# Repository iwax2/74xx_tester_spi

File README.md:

# 74xx_tester_spi

電気系の実験で用いる74LSxxシリーズ、学校の実験で壊れているかどうかチェックするのが大変なので、簡単にテストできるテス
タを作りました。
Arduinoシールド型（ちょっとでかい）で、0.5秒ぐらいでICを1つテストできます。
これはSPIでI/Oエキスパンダ(MCP23S17-E/SP)を接続するバージョンです。I2Cの(MCP23017-E/SP)も作る予定。

## つかうもの
* Arduino uno(互換品でも可)
* MCP23S17-E/SP(<http://akizukidenshi.com/catalog/g/gI-10644/>)
* ArduinoのLiquidCrystalクラスが使えるLCD(SC162Cなど)
* 14pin以上のソケット(できればゼロプレッシャー) こんなの -> <http://www.aitendo.com/product/12374>
* タクトスイッチ2つ
* Arduinoシールド台（基板加工機を使って作る、PCB製造業者に依頼する、自分でエッチングする、Arduino用のユニバーサル基板シールドを加工する、[ユニバーサル](http://diary-kuzenikike.blogspot.jp/2010/03/arduino.html "Arduino用のユニバーサル基板をつくる")[基板Cで頑張る](http://memo.tank.jp/archives/1182 "頑丈な自作プロトシールド")　など）

## 対応IC
*  "IV1 (74LS04)", // 1-input NOT
*  "AN2 (74LS08)", // 2-input AND
*  "OR2 (74LS32)", // 2-input OR
*  "ND2 (74LS00)", // 2-input NAND
*  "NR2 (74LS02)", // 2-input NOR
*  "EO2 (74LS86)", // 2-input XOR
*  "DFF (74LS74)"  // D flip-flop

## つかいかた
1. Arduinoにシールドを指します
2. テストしたいICをゼロプレッシャーソケットにセットします
3. セットしたICの型番をselectボタンで選択します
4. testボタンを押して、OKが出れば正常、NGが出れば壊れています

## Arduinoへのスケッチの書き込み
`tester_74xx_spi.ino`をArduino IDE (1.6.11で確認)で書き込んでください

## demo

## Pictures

全体写真

Arduinoシールドとして利用できる

テストした結果がOKの場合（壊れていないIC）

テストした結果がNGの場合（壊れているIC）

基板加工機(MITS AutoLab)で作成

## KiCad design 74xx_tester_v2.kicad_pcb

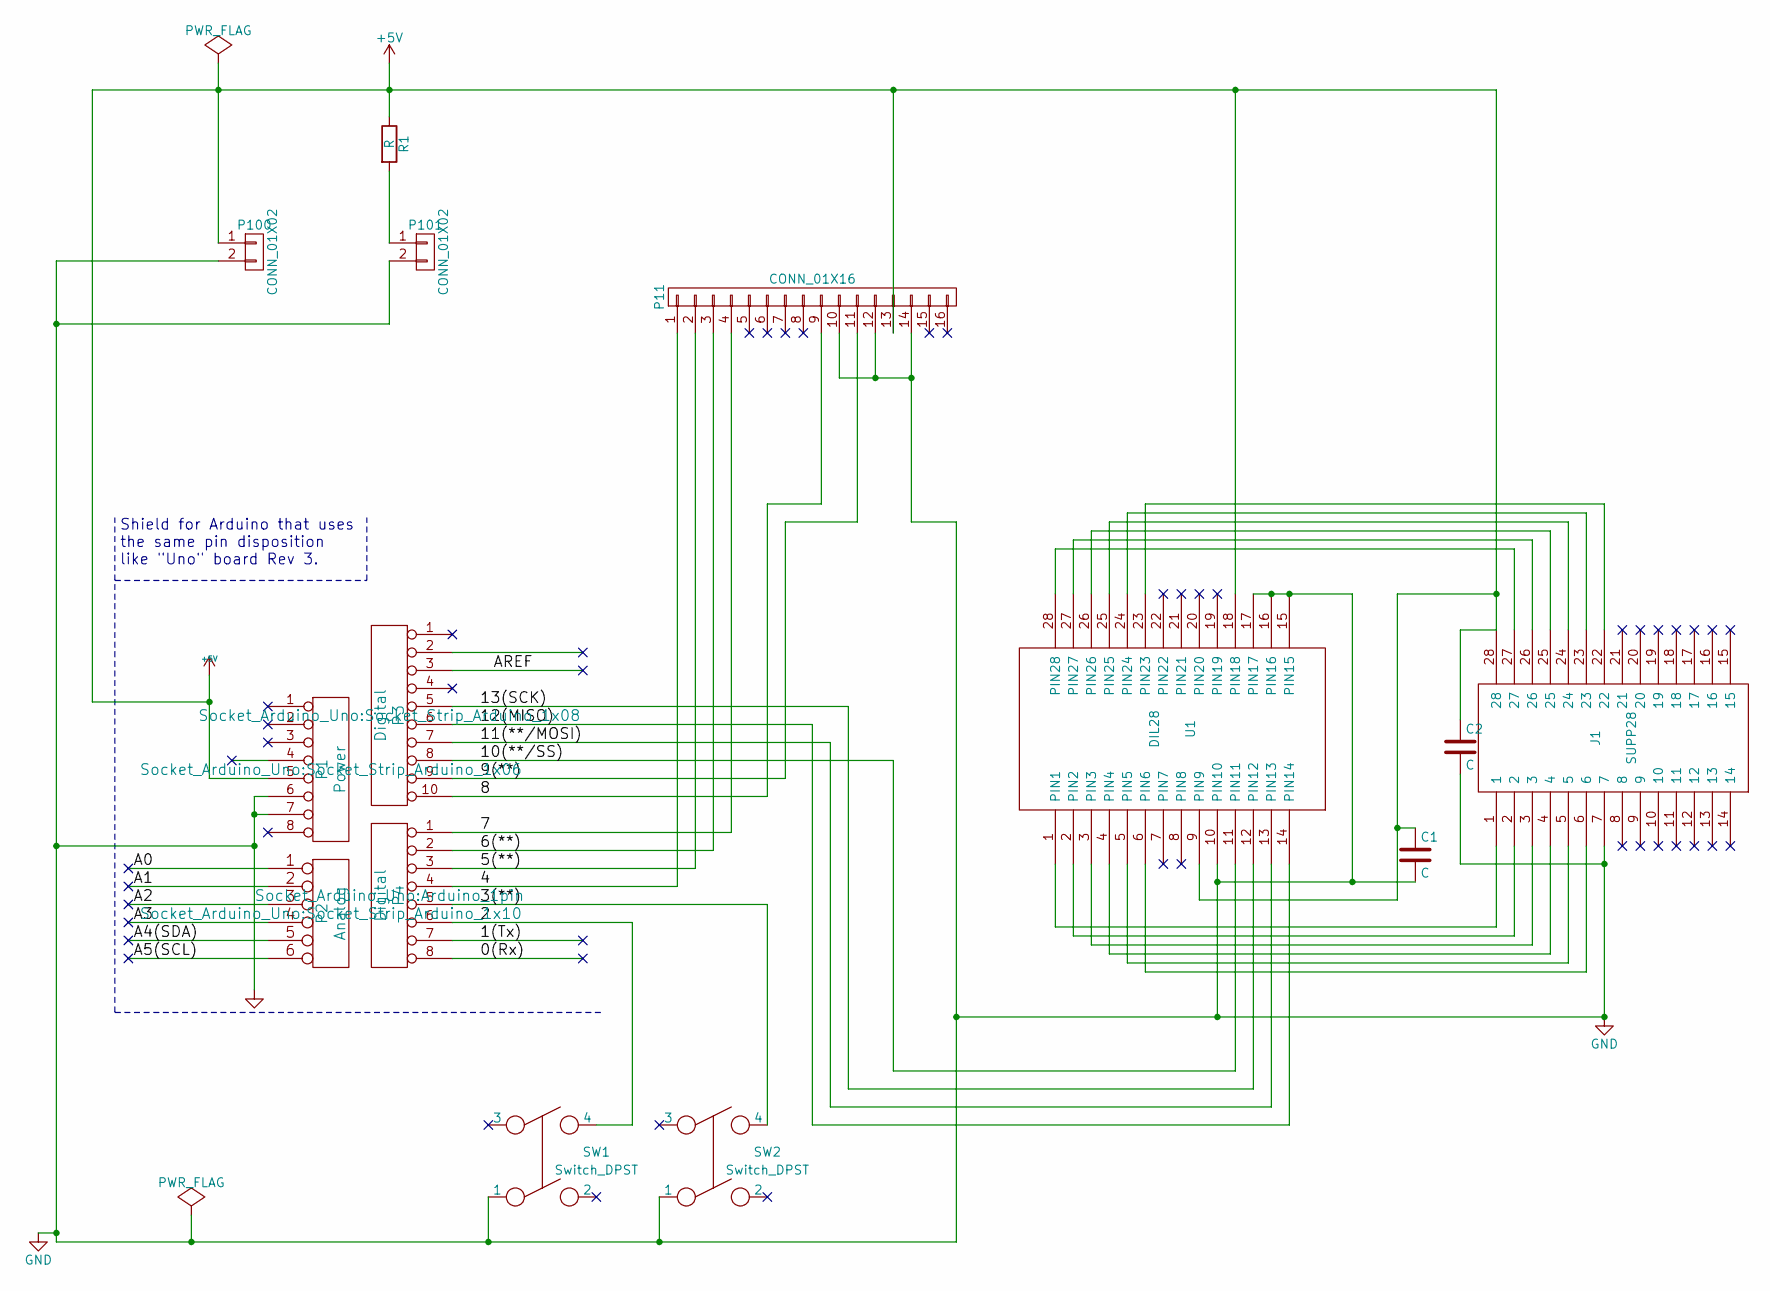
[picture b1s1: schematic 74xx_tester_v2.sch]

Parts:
C1, C2: C; C_0805_HandSoldering
J1: SUPP28; DIP-28_W15.24mm
P1: Power; Socket_Strip_Arduino_1x06
P2: Analog; Socket_Strip_Arduino_1x10
P3: Digital; Socket_Strip_Arduino_1x08
P4: Digital; Arduino_1pin
P11: CONN_01X16; Socket_Strip_Straight_1x16
P100, P101: CONN_01X02; Socket_Strip_Straight_1x02
R1: R; R_Axial_DIN0411_L9.9mm_D3.6mm_P7.62mm_Vertical
SW1, SW2: Switch_DPST; SW_TH_Tactile_Omron_B3F-10xx
U1: DIL28; DIP-28_W7.62mm

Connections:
+5V: C1.1, C2.1, J1.28, P1.5, P11.13, P100.1, R1.1, U1.9 (PIN9), U1.18 (PIN18)
/0(Rx): P4.8
/1(Tx): P4.7
/2: P4.6, SW1.4
/3(**): P4.5, SW2.4
/4: P4.4, P11.1
/5(**): P4.3, P11.2
/6(**): P4.2, P11.3
/7: P4.1, P11.4
/8: P3.10, P11.9
/9(**): P3.9, P11.11
/10(**/SS): P3.8, U1.11 (PIN11)
/11(**/MOSI): P3.7, U1.13 (PIN13)
/12(MISO): P3.6, U1.14 (PIN14)
/13(SCK): P3.5, U1.12 (PIN12)
/A0: P2.1
/A1: P2.2
/A2: P2.3
/A3: P2.4
/A4(SDA): P2.5
/A5(SCL): P2.6
/AREF: P3.3
GND: C1.2, C2.2, J1.7, P1.6, P1.7, P11.10, P11.12, P11.14, P100.2, P101.2, SW1.1, SW2.1, U1.10 (PIN10), U1.15 (PIN15), U1.16 (PIN16), U1.17 (PIN17)
unnamed: J1.1, U1.1 (PIN1)
unnamed: J1.2, U1.2 (PIN2)
unnamed: J1.3, U1.3 (PIN3)
unnamed: J1.4, U1.4 (PIN4)
unnamed: J1.5, U1.5 (PIN5)
unnamed: J1.6, U1.6 (PIN6)
unnamed: J1.22, U1.23 (PIN23)
unnamed: J1.23, U1.24 (PIN24)
unnamed: J1.24, U1.25 (PIN25)
unnamed: J1.25, U1.26 (PIN26)
unnamed: J1.26, U1.27 (PIN27)
unnamed: J1.27, U1.28 (PIN28)
unnamed: P101.1, R1.2

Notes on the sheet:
Shield for Arduino that uses the same pin disposition like "Uno" board Rev 3.

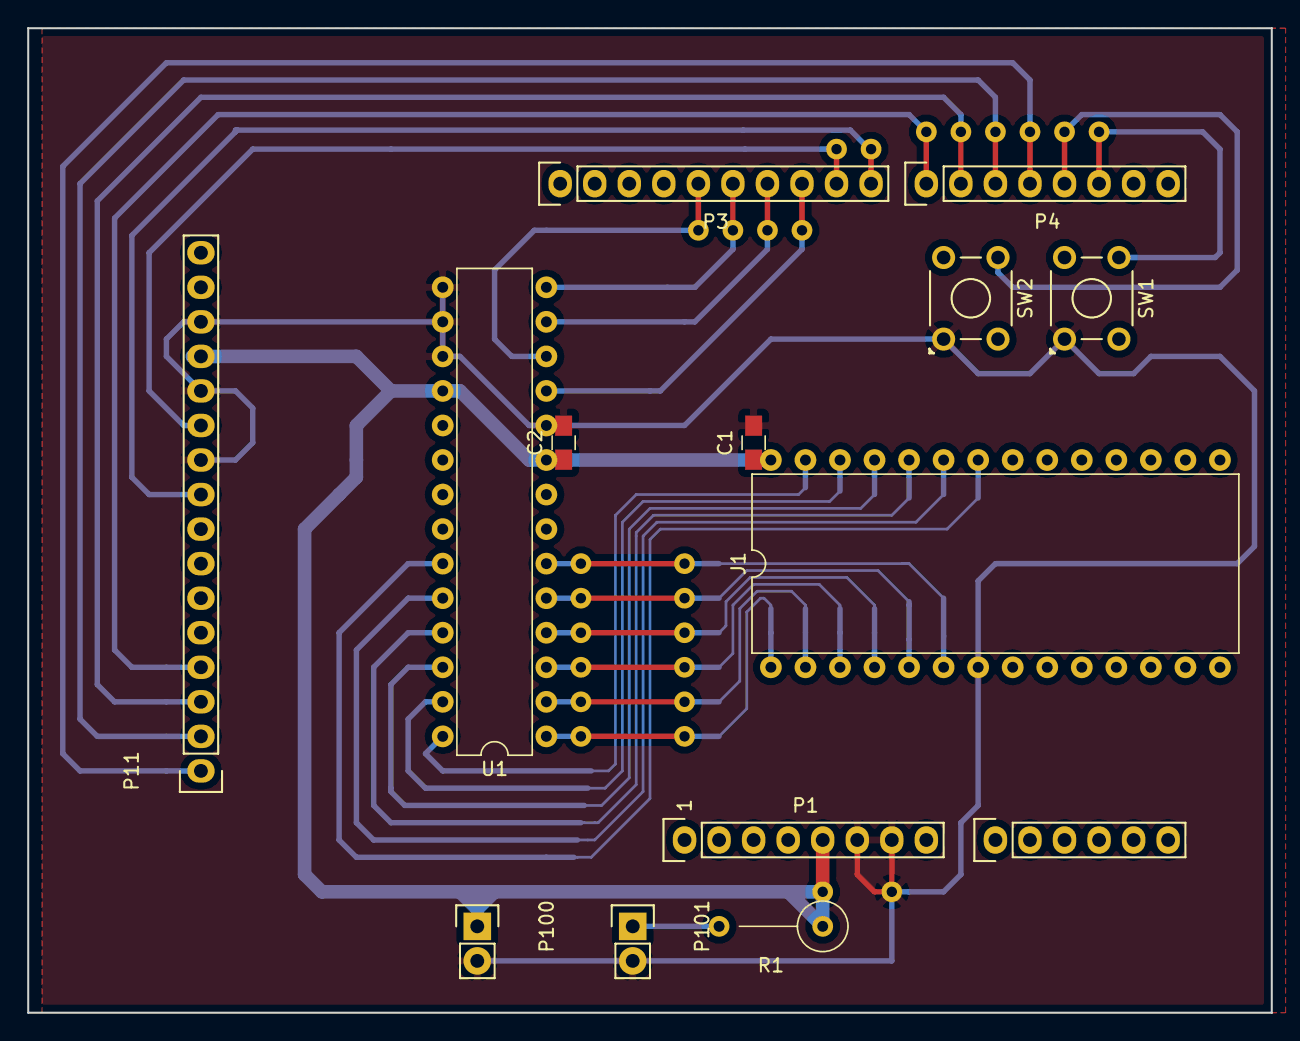
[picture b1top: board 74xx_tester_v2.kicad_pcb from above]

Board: 2 copper layers, 91.4 x 72.4 mm, 14 parts (0 on the bottom side), 27 nets.

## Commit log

2017-02-08 Add files arduino source and KiCad PCB data
2017-02-08 写真を追加
2017-02-09 add demo movies testing ICs
2017-02-09 upload demo video
